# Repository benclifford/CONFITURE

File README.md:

# CONFITURE

A co-routine based executive for a NeoPixel jamjar,
running on a Pi Pico (RP2040).

## Dramatis Personae

* A jam jar, jam eaten, jar de-labelled and washed
* Pi Pico (original)
* NeoPixel LED string (I blew up the first pixel, so I've cut it off)
* Adafruit CircuitPython 9.2.8
* Rotary encoder with push button

## Confiture v3 board

In kicad-test directory.

Fabricated x3 by aisler.

This works.

Problems to fix if I make v4:

i) the mounting holes for USB connector are too small, so the connector
rides a bit high and is not as securely connected as I want.

ii) There is no facility for protective capacitor and resistor. This is
fine for small battery powered projects, but it would be nice to have
the option to add: for capacitor, this could be entirely optional points
across the power bus. For the resistor, probably ok to make it compulsory
with an option to use a direct link not a resistor when placing components.

iii) v. minor some of the writing is off the side of the board or
hidden by components. This could all be tidied up.

iv) add cable tie strain relief hole

## minicom

To talk to micropython:

minicom --device=/dev/ttyACM0 --baud=115200

then press ctrl-C to interrupt and get a python prompt -- otherwise it
sits there with no output as it runs the LEDs.

## third party drivers

neopixel.py in this repo is neopixel.py from
0ba2f2122a54a71b1bc3576f87b1ba7dfc9db11e of 
https://github.com/adafruit/Adafruit_CircuitPython_NeoPixel/

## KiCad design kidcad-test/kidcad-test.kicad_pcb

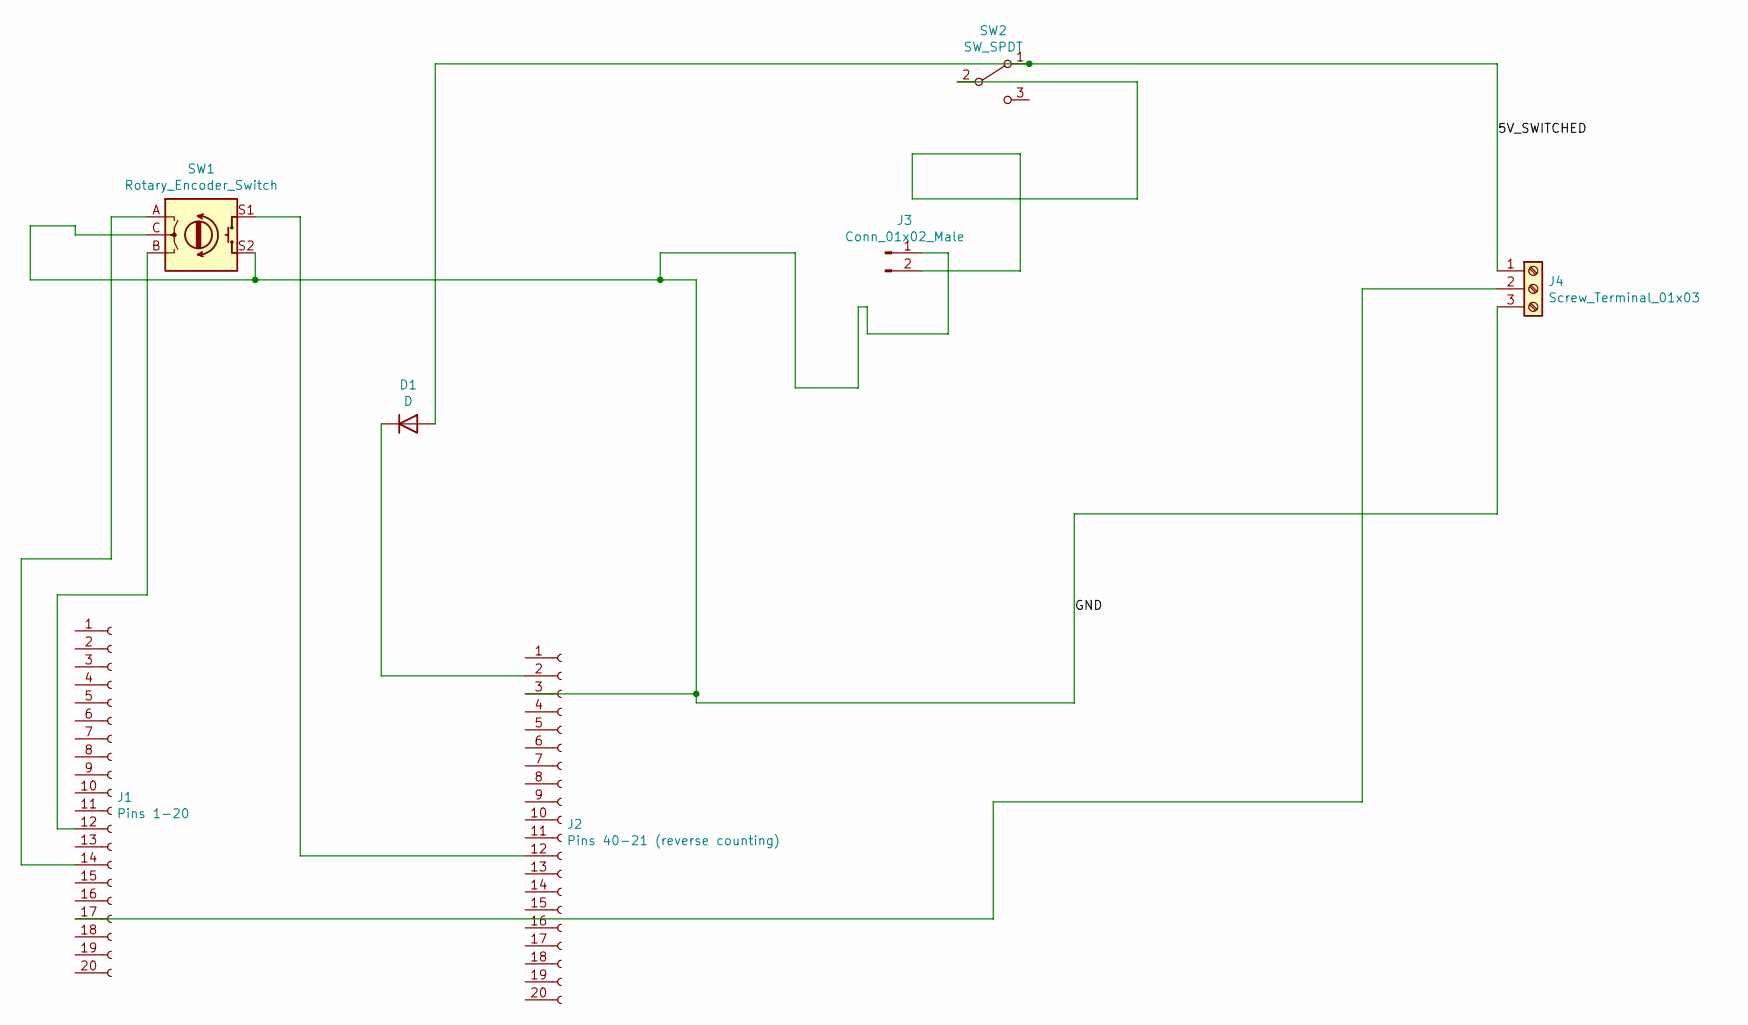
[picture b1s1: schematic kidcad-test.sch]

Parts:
D1: D; D_DO-41_SOD81_P10.16mm_Horizontal
J1: Pins 1-20; PinHeader_1x20_P2.54mm_Vertical
J2: Pins 40-21 (reverse counting); PinHeader_1x20_P2.54mm_Vertical
J3: Conn_01x02_Male; usb_micro_b_power_pp_benc
J4: Screw_Terminal_01x03; PinHeader_1x03_P2.54mm_Vertical
SW1: Rotary_Encoder_Switch; RotaryEncoder_Alps_EC11E-Switch_Vertical_H20mm
SW2: SW_SPDT; PinHeader_1x03_P2.54mm_Vertical

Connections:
/5V_SWITCHED: D1.2 (A), J4.1, SW2.1 (A)
/GND: J2.3, J3.1, J4.3, SW1.C, SW1.S2
unnamed: D1.1 (K), J2.2
unnamed: J1.12, SW1.B
unnamed: J1.14, SW1.A
unnamed: J1.17, J4.2
unnamed: J2.12, SW1.S1
unnamed: J3.2, SW2.2 (B)

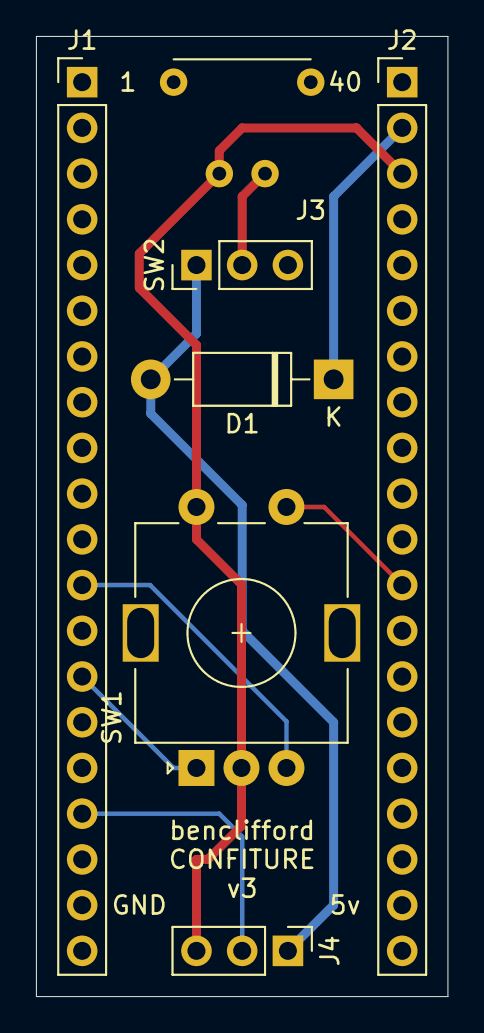
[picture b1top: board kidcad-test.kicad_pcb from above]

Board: 2 copper layers, 22.9 x 53.3 mm, 7 parts (0 on the bottom side), 8 nets.

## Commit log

2021-03-27 Import hacking from board
2021-03-27 Add readme
2021-03-27 Add jam jar to bill of materials
2021-03-27 Basic supervisor that toggles between two modes using rotary encoder
2021-03-27 port primaryswitcher2
2021-03-27 port contr2
2021-03-27 remove contr1 - too boring
2021-03-27 port phase1
2021-03-27 port rgb1
2021-03-27 make contr2 cycle through hues
2021-03-28 Make code.py importable rather than taking over when it is imported
2021-03-30 Change timing loop to measure time not iterations
2021-03-30 add fountain1 mode
2021-03-30 Start in whichever mode is at the start of the mode list, for consistency of control dial
2021-03-30 Add contr3 mode
2021-03-31 add threepart1 mode, and realise i should have used cos not sin for hue_saturated (although it hasn't affected any earlier modes, other than a phase shift)
2021-03-31 add vert1 mode
2021-03-31 add vert2 mode
2021-04-01 Add centre1 mode
2021-04-01 add huespin1 mode
2021-04-01 add drip1 mode
2021-04-01 add rainbow1 mode
2021-04-01 add mode huespin2
2021-04-01 Make huespin2 clear pixels at start
2021-04-01 add huespin3
2021-04-02 add huespin4 mode
2021-04-02 add huespin5 mode
2021-04-02 add huespin6 mode
2021-04-03 add pixphase1 mode
2021-04-04 Move neopixels to a pin more convenient for protoboard
2021-04-04 Move rotary encoders to pins more convenient for permaproto: further down board, and either side of a GND
2021-04-05 Move rotary encoder even further down the board
2021-04-05 Add input for the rotary encoder button for testing at REPL
2021-06-06 Add third party firmware image for completeness
2021-06-06 reconfigure to 2nd board (different pin, 1 more LED)
2021-06-06 Add configuration file for LED pin and number of LEDs
2021-06-06 Log mode number on change
2021-06-06 Tidy configuration
2021-06-06 Implement basic toggle between static and dynamic mode lists
2021-06-06 Use partial application to parameterise a solid colour mode
2021-06-06 Add more solid colour modes
2021-06-06 Add static solid random modes
2021-06-06 Add saturated rainbow static mode
2021-06-06 Switch to yield-based effects for delays, to potentially allow faster mode change implementation
2021-06-06 Add static white every n, with n adjustable
2021-06-06 Replace every-n with fraction/dither based that has a slightly more interesting pattern
2021-06-06 Replace solid modes with saturated-by-hue modes for same effect but better progammability
2021-06-06 Replace explicitly enumerated partial applications with procedurally generated list
2021-06-06 Add firefly mode
2021-06-06 colourise firefly a bit
2021-06-06 Reduce firefly state if no stimulus
2021-06-06 Pull firefly colouring function out for experimentation with colour schemes
2021-06-06 Add parameterisation of colours for firefly dynamic mode
2021-06-06 Add rainbow over 1/3rd of colour wheel, adjustable static mode
2021-06-06 Tweak steps for sequenced modes
2021-06-06 Add nightlight mode
2021-06-06 Add constrasts static mode
2021-06-06 Use a better tau
2021-06-06 Go to autochange mode when entering dynamic mode, cancelled by manually picking a dynamic mode
2021-06-06 Debugging/fixing autochange mode
2021-06-07 replace hardcoded 48s with num_leds - 1 to accomodate 50 LED string
2021-06-07 Remove dead code
2021-06-07 Swap long pause effect for several shorter ones to allow event polling to happen faster
2021-06-08 Add all kicad files
2021-07-06 Add board v3 comments
2021-07-06 Update board v3 notes
2025-07-29 WIP snapshot - last modified file was Jun 21st, 2021
2025-07-29 minicom notes
2025-07-29 As imported from actual working board in July 2025, which has had non-version-controlled hacking on it
2025-07-29 configuration as actually used on mirella's board for the last few years - different pin, and one less LED due to breakage
2025-07-29 Upgrade CircuitPython and consequential needed neopixel.py upgrade from vendor. works on mirellas (broken rotary encoder) board
2025-07-29 clarify using original pi pico, because i'm beginning to experiment with pico w and pico 2 w too
2025-07-29 Rotary encoder pins as used on confiture v3 board (flipped from what was in repo)
